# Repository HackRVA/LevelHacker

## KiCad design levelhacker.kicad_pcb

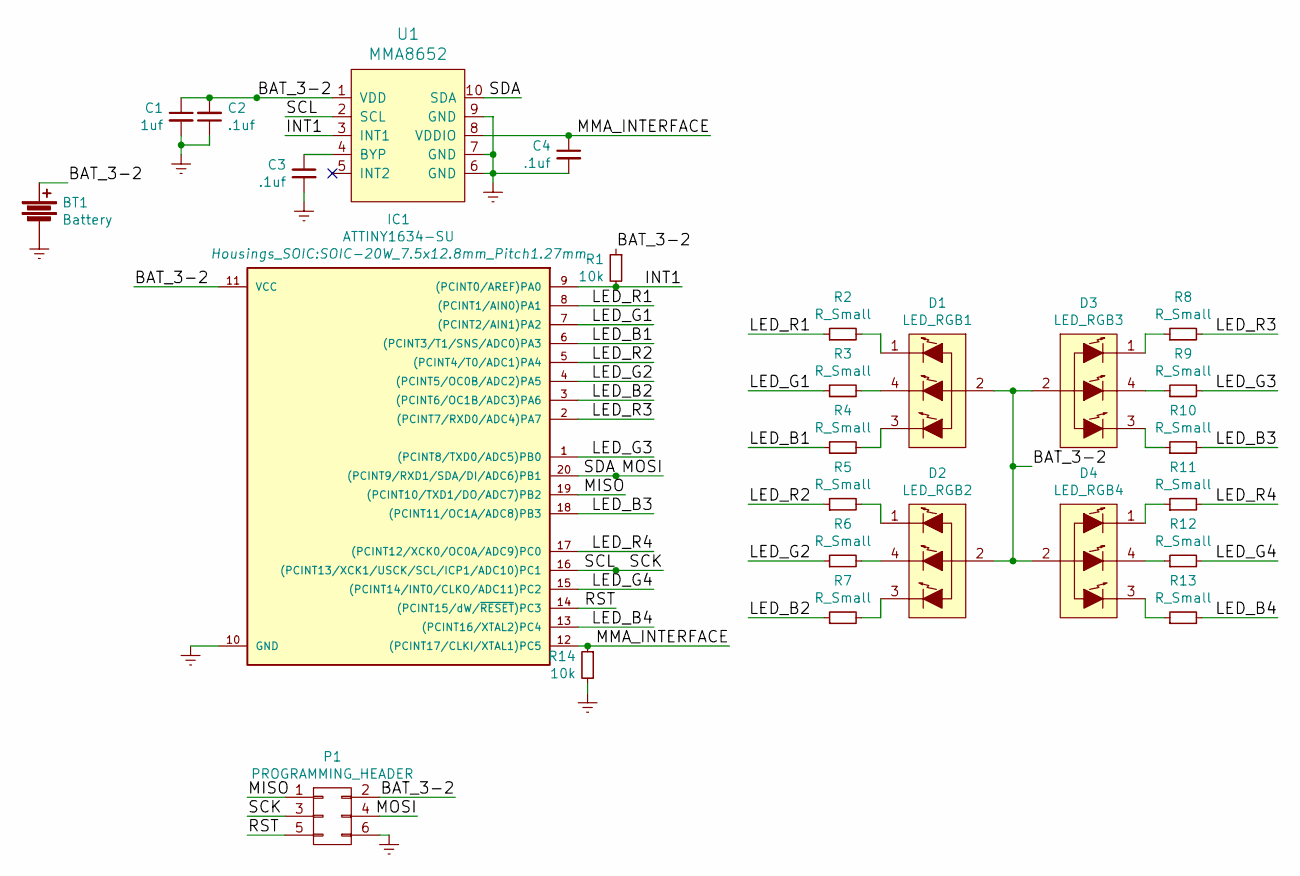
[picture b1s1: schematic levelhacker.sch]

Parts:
BT1: Battery; battery-2032
C1: 1uf; C_1206
C2, C3, C4: .1uf; C_1206
D1: LED_RGB1; LED_LUMEXLXT0805
D2: LED_RGB2; LED_LUMEXLXT0805
D3: LED_RGB3; LED_LUMEXLXT0805
D4: LED_RGB4; LED_LUMEXLXT0805
IC1: ATTINY1634-SU; SOIC-20W_7.5x12.8mm_Pitch1.27mm
P1: PROGRAMMING_HEADER; Pin_Header_Straight_SMT_02x03
R1, R14: 10k; R_1206
R2, R3, R4, R5, R6, R7, R8, R9, R10, R11, R12, R13: R_Small; R_1206
U1: MMA8652; DFN-10-1EP_2x2mm_Pitch0.4mm

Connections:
/BAT_3-2: BT1.1, C1.1, C2.2, D1.2 (COMMON_ANODE), D2.2 (COMMON_ANODE), D3.2 (COMMON_ANODE), D4.2 (COMMON_ANODE), IC1.11 (VCC), P1.2, R1.1, U1.1 (VDD)
/INT1: IC1.9 ((PCINT0/AREF)PA0), R1.2, U1.3 (INT1)
/LED_B1: IC1.6 ((PCINT3/T1/SNS/ADC0)PA3), R4.1
/LED_B2: IC1.3 ((PCINT6/OC1B/ADC3)PA6), R7.1
/LED_B3: IC1.18 ((PCINT11/OC1A/ADC8)PB3), R10.2
/LED_B4: IC1.13 ((PCINT16/XTAL2)PC4), R13.2
/LED_G1: IC1.7 ((PCINT2/AIN1)PA2), R3.1
/LED_G2: IC1.4 ((PCINT5/OC0B/ADC2)PA5), R6.1
/LED_G3: IC1.1 ((PCINT8/TXD0/ADC5)PB0), R9.2
/LED_G4: IC1.15 ((PCINT14/INT0/CLKO/ADC11)PC2), R12.2
/LED_R1: IC1.8 ((PCINT1/AIN0)PA1), R2.1
/LED_R2: IC1.5 ((PCINT4/T0/ADC1)PA4), R5.1
/LED_R3: IC1.2 ((PCINT7/RXD0/ADC4)PA7), R8.2
/LED_R4: IC1.17 ((PCINT12/XCK0/OC0A/ADC9)PC0), R11.2
/MISO: IC1.19 ((PCINT10/TXD1/DO/ADC7)PB2), P1.1
/MMA_INTERFACE: C4.1, IC1.12 ((PCINT17/CLKI/XTAL1)PC5), R14.1, U1.8 (VDDIO)
/MOSI: IC1.20 ((PCINT9/RXD1/SDA/DI/ADC6)PB1), P1.4, U1.10 (SDA)
/RST: IC1.14 ((PCINT15/dW/~RESET~)PC3), P1.5
/SCK: IC1.16 ((PCINT13/XCK1/USCK/SCL/ICP1/ADC10)PC1), P1.3, U1.2 (SCL)
Earth: BT1.2, C1.2, C2.1, C3.2, C4.2, IC1.10 (GND), P1.6, R14.2, U1.6 (GND), U1.7 (GND), U1.9 (GND)
unnamed: C3.1, U1.4 (BYP)
unnamed: D1.1 (RED_CATHODE), R2.2
unnamed: D1.3 (BLUE_CATHODE), R4.2
unnamed: D1.4 (GREEN_CATHODE), R3.2
unnamed: D2.1 (RED_CATHODE), R5.2
unnamed: D2.3 (BLUE_CATHODE), R7.2
unnamed: D2.4 (GREEN_CATHODE), R6.2
unnamed: D3.1 (RED_CATHODE), R8.1
unnamed: D3.3 (BLUE_CATHODE), R10.1
unnamed: D3.4 (GREEN_CATHODE), R9.1
unnamed: D4.1 (RED_CATHODE), R11.1
unnamed: D4.3 (BLUE_CATHODE), R13.1
unnamed: D4.4 (GREEN_CATHODE), R12.1

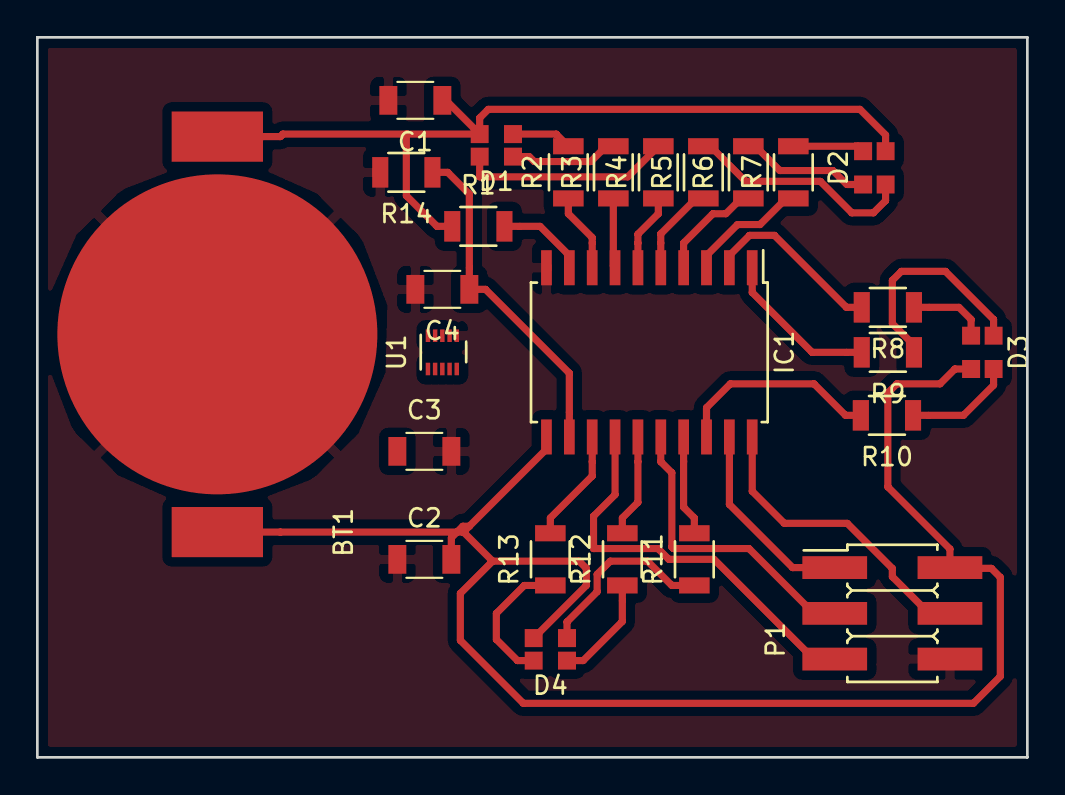
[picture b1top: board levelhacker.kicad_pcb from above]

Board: 2 copper layers, 55.0 x 40.0 mm, 26 parts (0 on the bottom side), 33 nets.

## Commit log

2017-02-16 Initial Commit and Schematic for an electronic level
2017-02-16 Add footprints for the RGB leds
2017-03-19 Add footprints for the coin cell battery and accel.
